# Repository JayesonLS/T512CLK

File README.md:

Schematics for the ATD T512CLK-A1 derived from Rob Krenicki's board layout
==========================================================================

There may be errors. That said, I found none in Rob Krenicki's work. KiCad's ERC and DRC checks likely caught all important errors in my work.

Do not produce the PCB layout from this KiCad project. Placing of standard KiCad parts onto the board has resulted in insufficient track spacing for production. If you wish to make a board, use Rob Krenicki's gerbers.

**Data point of note:** the required clock chip appears to be a DS1216B or DS1216C. I have tested a DS1216C successfully. I believe either variant will work given that no chip will be fitted into the DS1216. Note that this clock chip is not the more typical DS1216E SmartWatch chip for which there are reproductions. I have designed a replacement here: https://github.com/JayesonLS/SmartWatchRedux . Alternatively, used DS1216B or DS1216C's are still readily available from eBay, etc. They likely have dead batteries and an external replacement battery can be retrofitted with some work. Google "DS1216 battery replacement".

Software for the ATD-20 (or DS1216-C) clock fitted to a T512CLK-A1 is available from here: http://www.minuszerodegrees.net/rtc/rtc.htm . This software seems to correctly support current dates.

More information on the T512CLK is available from Rob Krenicki's project: https://github.com/rkrenicki/Tandy1000-DMA-Upgrade

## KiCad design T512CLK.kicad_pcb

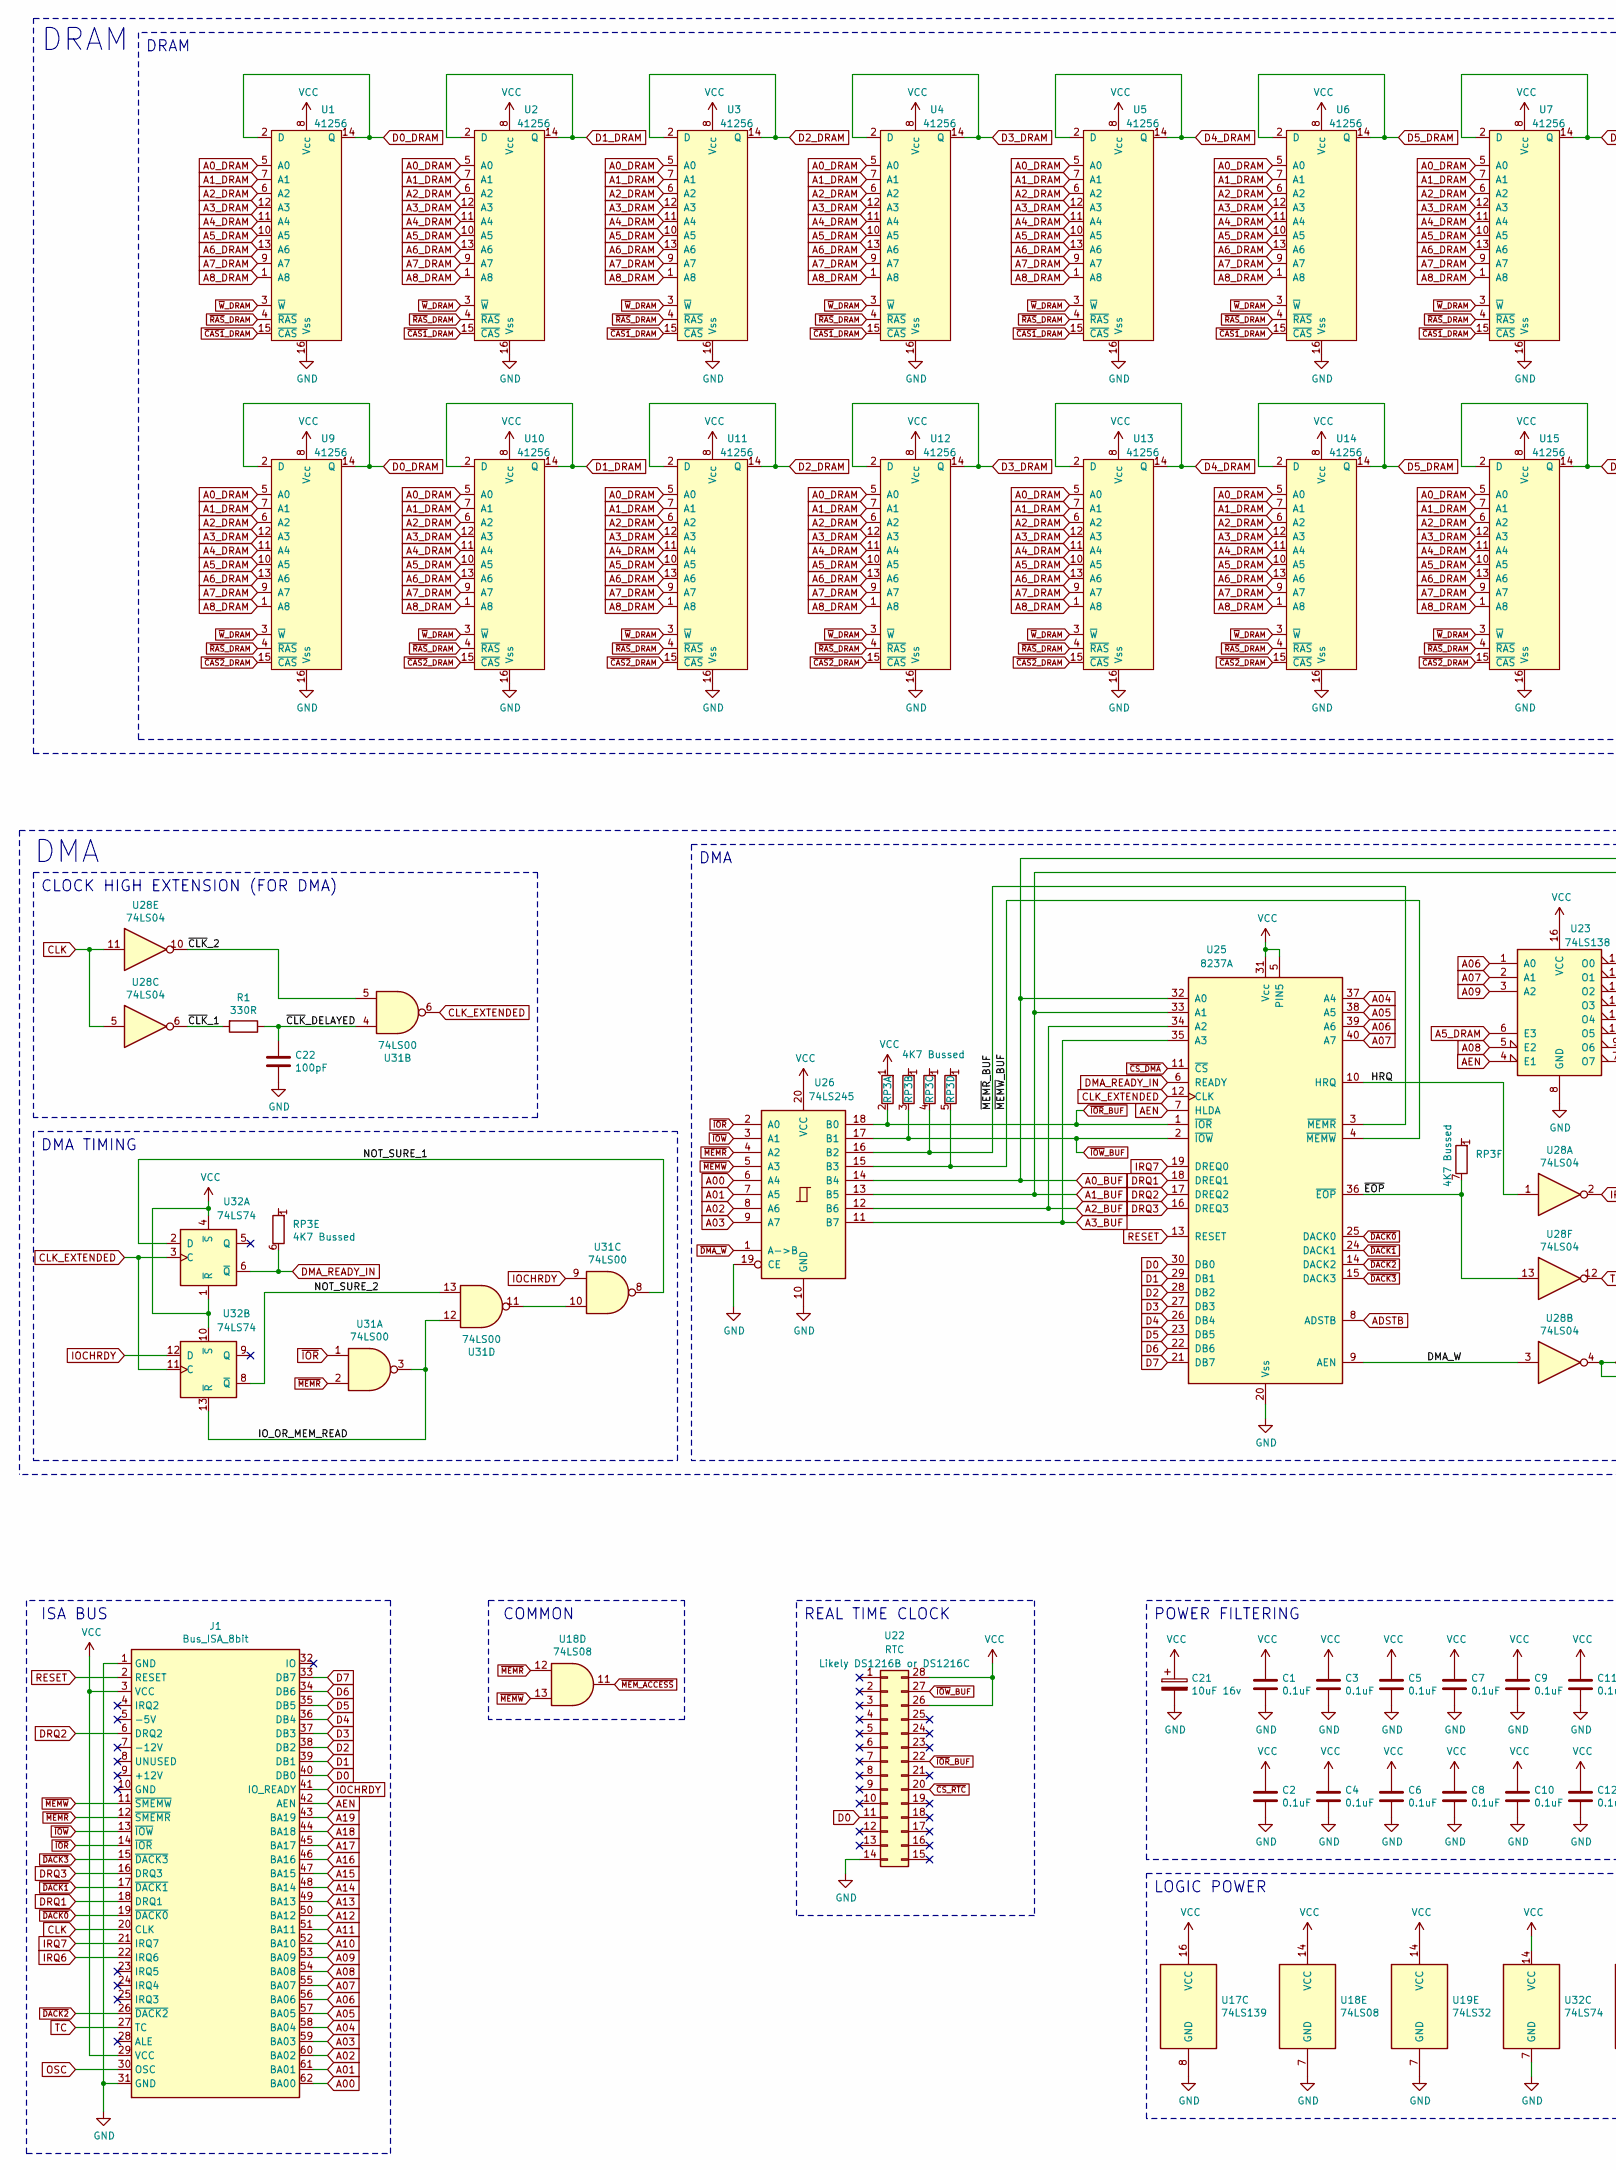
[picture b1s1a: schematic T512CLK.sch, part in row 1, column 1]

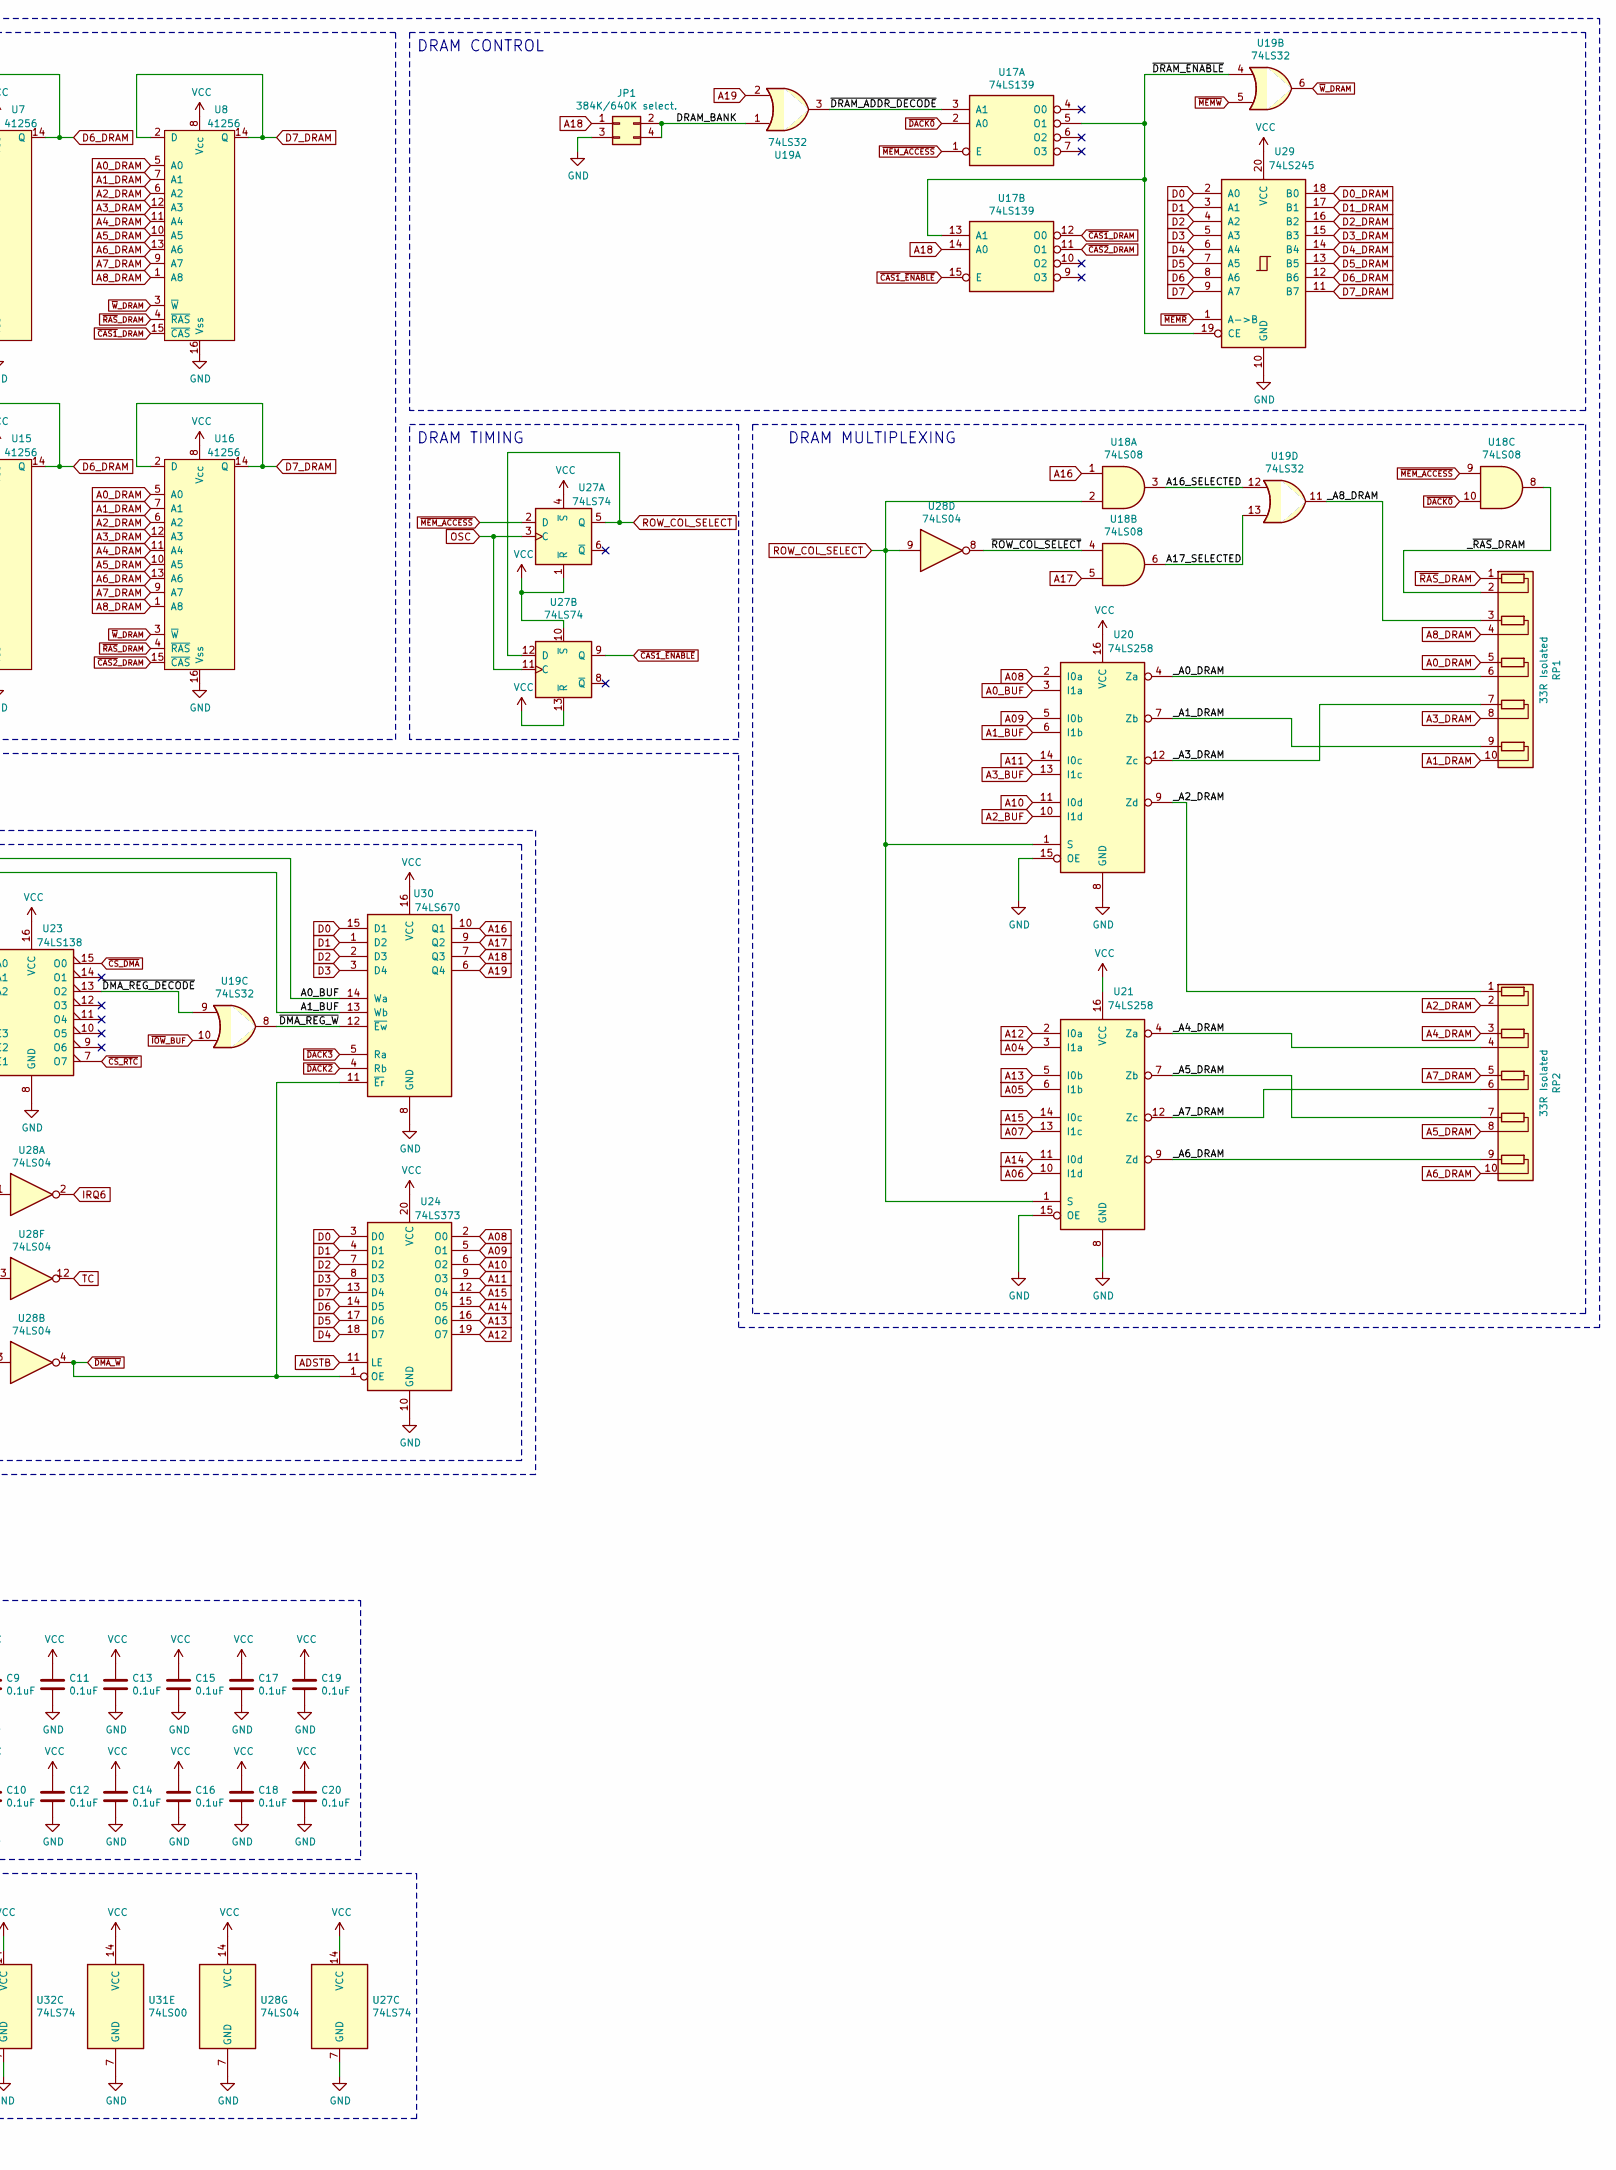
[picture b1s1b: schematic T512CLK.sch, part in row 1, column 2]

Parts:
C1, C2, C3, C4, C5, C6, C7, C8, C9, C10, C11, C12, C13, C14, C15, C16, C17, C18, C19, C20: 0.1uF; C_Ceramic
C21: 10uF 16v; CP_Radial_Tantal_D5.0mm_P2.50mm
C22: 100pF; C_Ceramic
J1: Bus_ISA_8bit; BUS_AT
JP1: 384K/640K select.; PinHeader_2x02_P2.54mm_Vertical
R1: 330R; R_Axial_DIN0309_L9.0mm_D3.2mm_P12.70mm_Horizontal
RP1, RP2: 33R Isolated; R_Array_SIP10
RP3: 4K7 Bussed; R_Array_SIP8
U1, U2, U3, U4, U5, U6, U7, U8, U9, U10, U11, U12, U13, U14, U15, U16: 41256; DIP-16_W7.62mm
U17: 74LS139; DIP-16_W7.62mm
U18: 74LS08; DIP-14_W7.62mm
U19: 74LS32; DIP-14_W7.62mm
U20, U21: 74LS258; DIP-16_W7.62mm
U22: RTC; DIP-28_W15.24mm
U23: 74LS138; DIP-16_W7.62mm
U24: 74LS373; DIP-20_W7.62mm
U25: 8237A; DIP-40_W15.24mm
U26, U29: 74LS245; DIP-20_W7.62mm
U27, U32: 74LS74; DIP-14_W7.62mm
U28: 74LS04; DIP-14_W7.62mm
U30: 74LS670; DIP-16_W7.62mm
U31: 74LS00; DIP-14_W7.62mm

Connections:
/A16_SELECTED: U18.3, U19.12
/A17_SELECTED: U18.6, U19.13
/DMA_W: U25.9 (AEN), U28.3
/DRAM_BANK: JP1.2, JP1.4, U19.1
/HRQ: U25.10 (HRQ), U28.1
/IO_OR_MEM_READ: U31.3, U31.12, U32.13 (~R)
/NOT_SURE_1: U31.8, U32.2 (D)
/NOT_SURE_2: U31.13, U32.8 (~Q)
/_A0_DRAM: RP1.6 (R3.2), U20.4 (Za)
/_A1_DRAM: RP1.9 (R5.1), U20.7 (Zb)
/_A2_DRAM: RP2.1 (R1.1), U20.9 (Zd)
/_A3_DRAM: RP1.7 (R4.1), U20.12 (Zc)
/_A4_DRAM: RP2.4 (R2.2), U21.4 (Za)
/_A5_DRAM: RP2.7 (R4.1), U21.7 (Zb)
/_A6_DRAM: RP2.9 (R5.1), U21.9 (Zd)
/_A7_DRAM: RP2.6 (R3.2), U21.12 (Zc)
/_A8_DRAM: RP1.3 (R2.1), U19.11
/_~RAS~_DRAM: RP1.2 (R1.2), U18.8
/~CLK~_1: R1.2, U28.6
/~CLK~_2: U28.10, U31.5
/~CLK~_DELAYED: C22.1, R1.1, U31.4
/~DMA_REG_DECODE: U19.9, U23.13 (O2)
/~DMA_REG_W: U19.8, U30.12 (~Ew)
/~DRAM_ADDR_DECODE: U17.3 (A1), U19.3
/~DRAM_ENABLE: U17.5 (O1), U17.13 (A1), U19.4, U29.19 (CE)
/~EOP: RP3.7 (R6.2), U25.36 (~EOP~), U28.13
/~MEMR~_BUF: RP3.4 (R3.2), U25.3 (~MEMR~), U26.16 (B2)
/~MEMW~_BUF: RP3.5 (R4.2), U25.4 (~MEMW~), U26.15 (B3)
/~ROW_COL_SELECT: U18.4, U28.8
A00: J1.62 (BA00), U26.6 (A4)
A0_BUF: U20.3 (I1a), U25.32 (A0), U26.14 (B4), U30.14 (Wa)
A0_DRAM: RP1.5 (R3.1), U1.5 (A0), U2.5 (A0), U3.5 (A0), U4.5 (A0), U5.5 (A0), U6.5 (A0), U7.5 (A0), U8.5 (A0), U9.5 (A0), U10.5 (A0), U11.5 (A0), U12.5 (A0), U13.5 (A0), U14.5 (A0), U15.5 (A0), U16.5 (A0)
A01: J1.61 (BA01), U26.7 (A5)
A1_BUF: U20.6 (I1b), U25.33 (A1), U26.13 (B5), U30.13 (Wb)
A1_DRAM: RP1.10 (R5.2), U1.7 (A1), U2.7 (A1), U3.7 (A1), U4.7 (A1), U5.7 (A1), U6.7 (A1), U7.7 (A1), U8.7 (A1), U9.7 (A1), U10.7 (A1), U11.7 (A1), U12.7 (A1), U13.7 (A1), U14.7 (A1), U15.7 (A1), U16.7 (A1)
A02: J1.60 (BA02), U26.8 (A6)
A2_BUF: U20.10 (I1d), U25.34 (A2), U26.12 (B6)
A2_DRAM: RP2.2 (R1.2), U1.6 (A2), U2.6 (A2), U3.6 (A2), U4.6 (A2), U5.6 (A2), U6.6 (A2), U7.6 (A2), U8.6 (A2), U9.6 (A2), U10.6 (A2), U11.6 (A2), U12.6 (A2), U13.6 (A2), U14.6 (A2), U15.6 (A2), U16.6 (A2)
A03: J1.59 (BA03), U26.9 (A7)
A3_BUF: U20.13 (I1c), U25.35 (A3), U26.11 (B7)
A3_DRAM: RP1.8 (R4.2), U1.12 (A3), U2.12 (A3), U3.12 (A3), U4.12 (A3), U5.12 (A3), U6.12 (A3), U7.12 (A3), U8.12 (A3), U9.12 (A3), U10.12 (A3), U11.12 (A3), U12.12 (A3), U13.12 (A3), U14.12 (A3), U15.12 (A3), U16.12 (A3)
A04: J1.58 (BA04), U21.3 (I1a), U25.37 (A4)
A4_DRAM: RP2.3 (R2.1), U1.11 (A4), U2.11 (A4), U3.11 (A4), U4.11 (A4), U5.11 (A4), U6.11 (A4), U7.11 (A4), U8.11 (A4), U9.11 (A4), U10.11 (A4), U11.11 (A4), U12.11 (A4), U13.11 (A4), U14.11 (A4), U15.11 (A4), U16.11 (A4)
A05: J1.57 (BA05), U21.6 (I1b), U25.38 (A5)
A5_DRAM: RP2.8 (R4.2), U1.10 (A5), U2.10 (A5), U3.10 (A5), U4.10 (A5), U5.10 (A5), U6.10 (A5), U7.10 (A5), U8.10 (A5), U9.10 (A5), U10.10 (A5), U11.10 (A5), U12.10 (A5), U13.10 (A5), U14.10 (A5), U15.10 (A5), U16.10 (A5), U23.6 (E3)
A06: J1.56 (BA06), U21.10 (I1d), U23.1 (A0), U25.39 (A6)
A6_DRAM: RP2.10 (R5.2), U1.13 (A6), U2.13 (A6), U3.13 (A6), U4.13 (A6), U5.13 (A6), U6.13 (A6), U7.13 (A6), U8.13 (A6), U9.13 (A6), U10.13 (A6), U11.13 (A6), U12.13 (A6), U13.13 (A6), U14.13 (A6), U15.13 (A6), U16.13 (A6)
A07: J1.55 (BA07), U21.13 (I1c), U23.2 (A1), U25.40 (A7)
A7_DRAM: RP2.5 (R3.1), U1.9 (A7), U2.9 (A7), U3.9 (A7), U4.9 (A7), U5.9 (A7), U6.9 (A7), U7.9 (A7), U8.9 (A7), U9.9 (A7), U10.9 (A7), U11.9 (A7), U12.9 (A7), U13.9 (A7), U14.9 (A7), U15.9 (A7), U16.9 (A7)
A08: J1.54 (BA08), U20.2 (I0a), U23.5 (E2), U24.2 (O0)
A8_DRAM: RP1.4 (R2.2), U1.1 (A8), U2.1 (A8), U3.1 (A8), U4.1 (A8), U5.1 (A8), U6.1 (A8), U7.1 (A8), U8.1 (A8), U9.1 (A8), U10.1 (A8), U11.1 (A8), U12.1 (A8), U13.1 (A8), U14.1 (A8), U15.1 (A8), U16.1 (A8)
A09: J1.53 (BA09), U20.5 (I0b), U23.3 (A2), U24.5 (O1)
A10: J1.52 (BA10), U20.11 (I0d), U24.6 (O2)
A11: J1.51 (BA11), U20.14 (I0c), U24.9 (O3)
A12: J1.50 (BA12), U21.2 (I0a), U24.19 (O7)
A13: J1.49 (BA13), U21.5 (I0b), U24.16 (O6)
A14: J1.48 (BA14), U21.11 (I0d), U24.15 (O5)
A15: J1.47 (BA15), U21.14 (I0c), U24.12 (O4)
A16: J1.46 (BA16), U18.1, U30.10 (Q1)
A17: J1.45 (BA17), U18.5, U30.9 (Q2)
A18: J1.44 (BA18), JP1.1, U17.14 (A0), U30.7 (Q3)
A19: J1.43 (BA19), U19.2, U30.6 (Q4)
ADSTB: U24.11 (LE), U25.8 (ADSTB)
AEN: J1.42 (AEN), U23.4 (E1), U25.7 (HLDA)
CLK: J1.20 (CLK), U28.5, U28.11
CLK_EXTENDED: U25.12 (CLK), U31.6, U32.3 (C), U32.11 (C)
D0: J1.40 (DB0), U22.11, U24.3 (D0), U25.30 (DB0), U29.2 (A0), U30.15 (D1)
D0_DRAM: U1.2 (D), U1.14 (Q), U9.2 (D), U9.14 (Q), U29.18 (B0)
D1: J1.39 (DB1), U24.4 (D1), U25.29 (DB1), U29.3 (A1), U30.1 (D2)
D1_DRAM: U2.2 (D), U2.14 (Q), U10.2 (D), U10.14 (Q), U29.17 (B1)
D2: J1.38 (DB2), U24.7 (D2), U25.28 (DB2), U29.4 (A2), U30.2 (D3)
D2_DRAM: U3.2 (D), U3.14 (Q), U11.2 (D), U11.14 (Q), U29.16 (B2)
D3: J1.37 (DB3), U24.8 (D3), U25.27 (DB3), U29.5 (A3), U30.3 (D4)
D3_DRAM: U4.2 (D), U4.14 (Q), U12.2 (D), U12.14 (Q), U29.15 (B3)
D4: J1.36 (DB4), U24.18 (D7), U25.26 (DB4), U29.6 (A4)
D4_DRAM: U5.2 (D), U5.14 (Q), U13.2 (D), U13.14 (Q), U29.14 (B4)
D5: J1.35 (DB5), U24.17 (D6), U25.23 (DB5), U29.7 (A5)
D5_DRAM: U6.2 (D), U6.14 (Q), U14.2 (D), U14.14 (Q), U29.13 (B5)
D6: J1.34 (DB6), U24.14 (D5), U25.22 (DB6), U29.8 (A6)
D6_DRAM: U7.2 (D), U7.14 (Q), U15.2 (D), U15.14 (Q), U29.12 (B6)
D7: J1.33 (DB7), U24.13 (D4), U25.21 (DB7), U29.9 (A7)
D7_DRAM: U8.2 (D), U8.14 (Q), U16.2 (D), U16.14 (Q), U29.11 (B7)
DMA_READY_IN: RP3.6 (R5.2), U25.6 (READY), U32.6 (~Q)
DRQ1: J1.18 (DRQ1), U25.18 (DREQ1)
DRQ2: J1.6 (DRQ2), U25.17 (DREQ2)
DRQ3: J1.16 (DRQ3), U25.16 (DREQ3)
GND: C1.2, C2.2, C3.2, C4.2, C5.2, C6.2, C7.2, C8.2, C9.2, C10.2, C11.2, C12.2, C13.2, C14.2, C15.2, C16.2, C17.2, C18.2, C19.2, C20.2, C21.2, C22.2, J1.1 (GND), J1.31 (GND), JP1.3, U1.16 (Vss), U2.16 (Vss), U3.16 (Vss), U4.16 (Vss), U5.16 (Vss), U6.16 (Vss), U7.16 (Vss), U8.16 (Vss), U9.16 (Vss), U10.16 (Vss), U11.16 (Vss), U12.16 (Vss), U13.16 (Vss), U14.16 (Vss), U15.16 (Vss), U16.16 (Vss), U17.8 (GND), U18.7 (GND), U19.7 (GND), U20.8 (GND), U20.15 (OE), U21.8 (GND), U21.15 (OE), U22.14, U23.8 (GND), U24.10 (GND), U25.20 (Vss), U26.10 (GND), U26.19 (CE), U27.7 (GND), U28.7 (GND), U29.10 (GND), U30.8 (GND), U31.7 (GND), U32.7 (GND)
IOCHRDY: J1.41 (IO_READY), U31.9, U32.12 (D)
IRQ6: J1.22 (IRQ6), U28.2
IRQ7: J1.21 (IRQ7), U25.19 (DREQ0)
unnamed: U31.10, U31.11
OSC: J1.30 (OSC), U27.3 (C), U27.11 (C)
RESET: J1.2 (RESET), U25.13 (RESET)
ROW_COL_SELECT: U18.2, U20.1 (S), U21.1 (S), U27.5 (Q), U27.12 (D), U28.9
TC: J1.27 (TC), U28.12
VCC: C1.1, C2.1, C3.1, C4.1, C5.1, C6.1, C7.1, C8.1, C9.1, C10.1, C11.1, C12.1, C13.1, C14.1, C15.1, C16.1, C17.1, C18.1, C19.1, C20.1, C21.1, J1.3 (VCC), J1.29 (VCC), RP3.1 (R1.1), U1.8 (Vcc), U2.8 (Vcc), U3.8 (Vcc), U4.8 (Vcc), U5.8 (Vcc), U6.8 (Vcc), U7.8 (Vcc), U8.8 (Vcc), U9.8 (Vcc), U10.8 (Vcc), U11.8 (Vcc), U12.8 (Vcc), U13.8 (Vcc), U14.8 (Vcc), U15.8 (Vcc), U16.8 (Vcc), U17.16 (VCC), U18.14 (VCC), U19.14 (VCC), U20.16 (VCC), U21.16 (VCC), U22.26, U22.28, U23.16 (VCC), U24.20 (VCC), U25.5 (PIN5), U25.31 (Vcc), U26.20 (VCC), U27.1 (~R), U27.4 (~S), U27.10 (~S), U27.13 (~R), U27.14 (VCC), U28.14 (VCC), U29.20 (VCC), U30.16 (VCC), U31.14 (VCC), U32.1 (~R), U32.4 (~S), U32.10 (~S), U32.14 (VCC)
~CAS1~_DRAM: U1.15 (~CAS), U2.15 (~CAS), U3.15 (~CAS), U4.15 (~CAS), U5.15 (~CAS), U6.15 (~CAS), U7.15 (~CAS), U8.15 (~CAS), U17.12 (O0)
~CAS1~_~ENABLE: U17.15 (E), U27.9 (Q)
~CAS2~_DRAM: U9.15 (~CAS), U10.15 (~CAS), U11.15 (~CAS), U12.15 (~CAS), U13.15 (~CAS), U14.15 (~CAS), U15.15 (~CAS), U16.15 (~CAS), U17.11 (O1)
~CS_DMA: U23.15 (O0), U25.11 (~CS~)
~CS_RTC: U22.20, U23.7 (O7)
~DACK0: J1.19 (~DACK0), U17.2 (A0), U18.10, U25.25 (DACK0)
~DACK1: J1.17 (~DACK1), U25.24 (DACK1)
~DACK2: J1.26 (~DACK2), U25.14 (DACK2), U30.4 (Rb)
~DACK3: J1.15 (~DACK3), U25.15 (DACK3), U30.5 (Ra)
~DMA_W: U24.1 (OE), U26.1 (A->B), U28.4, U30.11 (~Er)
~IOR: J1.14 (~IOR), U26.2 (A0), U31.1
~IOR~_BUF: RP3.2 (R1.2), U22.22, U25.1 (~IOR~), U26.18 (B0)
~IOW: J1.13 (~IOW), U26.3 (A1)
~IOW~_BUF: RP3.3 (R2.2), U19.10, U22.27, U25.2 (~IOW~), U26.17 (B1)
~MEMR: J1.12 (~SMEMR), U18.12, U26.4 (A2), U29.1 (A->B), U31.2
~MEMW: J1.11 (~SMEMW), U18.13, U19.5, U26.5 (A3)
~MEM_ACCESS: U17.1 (E), U18.9, U18.11, U27.2 (D)
~RAS~_DRAM: RP1.1 (R1.1), U1.4 (~RAS), U2.4 (~RAS), U3.4 (~RAS), U4.4 (~RAS), U5.4 (~RAS), U6.4 (~RAS), U7.4 (~RAS), U8.4 (~RAS), U9.4 (~RAS), U10.4 (~RAS), U11.4 (~RAS), U12.4 (~RAS), U13.4 (~RAS), U14.4 (~RAS), U15.4 (~RAS), U16.4 (~RAS)
~W~_DRAM: U1.3 (~W), U2.3 (~W), U3.3 (~W), U4.3 (~W), U5.3 (~W), U6.3 (~W), U7.3 (~W), U8.3 (~W), U9.3 (~W), U10.3 (~W), U11.3 (~W), U12.3 (~W), U13.3 (~W), U14.3 (~W), U15.3 (~W), U16.3 (~W), U19.6

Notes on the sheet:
REAL TIME CLOCK
POWER FILTERING
LOGIC POWER
DRAM
ISA BUS
DMA TIMING
DMA
CLOCK HIGH EXTENSION (FOR DMA)
COMMON
DRAM CONTROL
DRAM MULTIPLEXING
DRAM TIMING

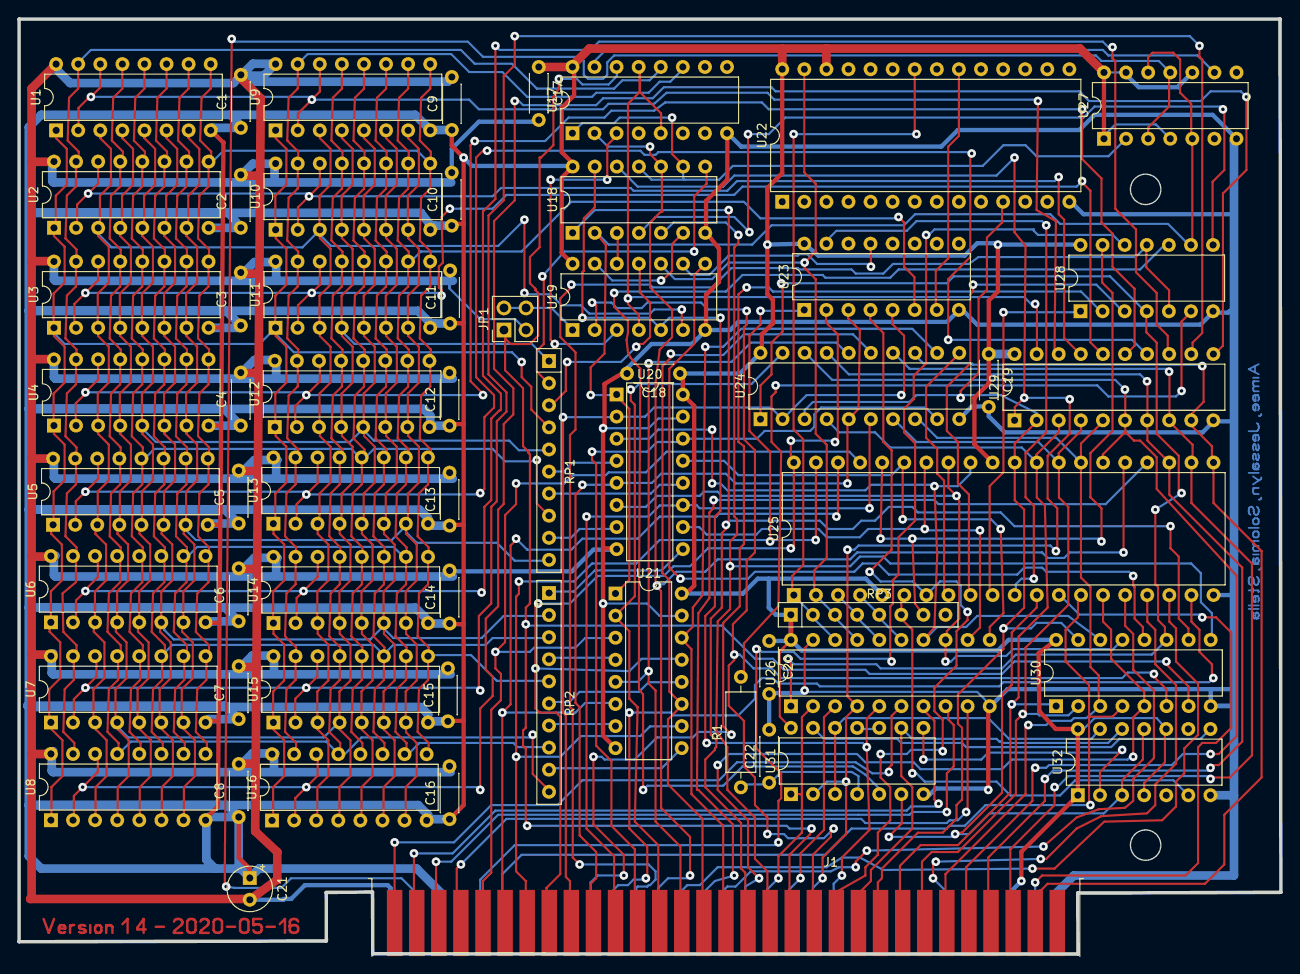
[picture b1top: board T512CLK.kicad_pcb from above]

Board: 2 copper layers, 145.1 x 107.5 mm, 60 parts (0 on the bottom side), 115 nets.

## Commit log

2021-02-26 Add rkrenicki's Gerbers.
2021-02-26 Change RP3 symbol from a single to split for better readability.
2021-02-26 Add first complete pass of KiCad project.
2021-02-26 Change RP1 and RP2 symbols from single to split for better readability.
2021-02-26 Update PDF schematic plot.
